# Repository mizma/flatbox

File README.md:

# Flatbox-ACR

_**No longer maintained.**_

**New Design is available [Here](https://github.com/mizma/ergoSHIFT/) with 11 button support and GP2040-CE firmware support planned**

_**Low profile hitbox-layout fightstick with Acrylic shell**_

This flatbox-acr design is based on [jfedor2/flatbox](https://github.com/jfedor2/flatbox) but with a few tweaks
(rev1.1 pcb has been redone from ground up):

[日本語はこちら](README_ja.md)

* Replaced the 3D printed case with Acrylic shell, allowing to insert printed artwork.
    * or marvel at the simplistic PCB...
    * Heavily inspired by y [Mille-Feuille](https://pomegd.booth.pm/items/2685530) by [@pomegd](https://twitter.com/pomegd)
* modified button layout to:
    * Accomodate for the clearance needed for acrylic cutting
    * To mimic the layout of the original Hitbox button layout(based off of official stencil)
* Silk screen update
    * Added small logo instead of text (flatbox acr)
    * added legends for each buttons (SQUARE, CIRCLE etc.)
    * moved logo to the bottom edge to minimize see-through when adding artwork on top
* Pattern changes
    * GND Fill
    * add vias to join gnd fill
    * moved traces slightly to avoid GND islands and thin GND fills
    * added reset button for Pro Micro board
* Remodeled Button Caps to accomodate for the increased case-height

Final product when assembled will look something like the following:

You can print any fan art using the [Stencil](hardware-rev1.1/images/Flatbox-ACR-Stencil_300dpi.png) 
to customize the looks as well.

(*) Artwork based on a trace of In-Game Screenshot + Official Fan-kit (©ARK SYSTEM WORKS)

There is currently one revision of the Flatbox-ACR.  They all use Kailh low profile (choc v1) mechanical keyboard switches.
The table below lists their main features.  See the README for each version for details on how to make them.

version | [rev1.1](hardware-rev1.1) |
------- | ------------------------- |
case dimensions | 210x125x13.6mm |
compatibility (using provided firmware) | PC, PS3, Xinput, Switch |
add-on board | Sparkfun Qwiic Pro Micro |
onboard chip | - |
port | USB-C |
SMT assembly required | no |
firmware | [ATmega32U4](firmwares_atmega32u4) |

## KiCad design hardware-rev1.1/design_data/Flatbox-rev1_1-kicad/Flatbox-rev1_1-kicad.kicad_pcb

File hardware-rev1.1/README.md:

# Flatbox-ACR rev1.1

[日本語はこちら](README_ja.md)

This is rev1.1 of the Flatbox-ACR. In this version an Arduino Pro Micro is soldered onto the main PCB.

To make one you will need:

* [acrylic shell](acrylic-shell)
    * Top layers in 2mm,3mm,2mm thickness
    * Bottom layers in 3mm thickness x 2
* [the Flatbox-ACR PCB](pcb)
* Arduino Pro Micro [SparkFun Qwiic Pro Micro - USB-C (ATmega32U4)](https://www.sparkfun.com/products/15795)
* 12x Kailh low profile (choc v1) switches of your choice
    * I use Kailh Choc v1 Red Pro (Linear and low activation force: 35±10gf with actuation travel: 1.5±0.5mm)
    * Light Blue (gChoc) can be used for even lower actuation force.
* (optionally) 12x Kailh low profile hotswap sockets
* [3D printed buttoncaps](../3d-printed-buttoncaps)
* 6x 6x6x5mm tact switches
    * I Used OMRON B3F-1000 but other similar products with same footprint should work
    * Selecting switches with height higher than 7mm will result in the switch extruding from the case
* 1x 3x6x4.3 horizontal tact switch
    * https://www.newegg.com/p/2S7-01KR-035X0
    * https://shop.yushakobo.jp/collections/all-keyboard-parts/products/a1600ed-01-1
    * [schematics](images/tactile-switch_3x6x4.3.jpg)
* 7x M3 screws (length 20mm)
    * Acryl top 2mm * 2 + 3mm = 7mm
    * PCB 1.6mm
    * Acryl bottom 3mm * 2 = 6mm
    * Rubber feet screw depth = 3mm (using rubber feet below.  adjust for your part)
    * Rubber feet total depth = 8mm (using rubber feet below.  adjust for your part)
    * M3 nut height = 2mm
    * min length = 19.6mm (using rubber feet below.  adjust for your part)
    * max length = 22.6mm (using rubber feet below.  adjust for your part)
* 7x M3 nut and acompanying rubber feet
    * Rubber feet Tochigiya [TM-TK-15](https://www.monotaro.com/p/0933/2486/?displayId=5)
    * The position of the holes are intended for feet radius of less than 8mm
* a soldering iron
    * something with enough power is better 
      (i.e. [Hakko FX 600](https://www.hakko.com/japan/products/hakko_fx600_set.html))
    * I recommend changin tips to D type for most Through-hole soldering, or C type if you plan to
      solder SMT as well. (default B tips are the harder to use for most PCB soldering)
    * Use 230C ~ 250C temp recommended (can be changed if you know your way around)

## Assembly Instructions

### Ordering PCB

I used [JLCPCB](https://jlcpcb.com/).  Just upload the gerber files in [pcb](pcb) and keep most parameters default.
You may change PCB Qty and PCB Color if you like.  All other parameters should be kept the same.

### Ordering 3D Printed Buttons

If you have a 3D printer, print at your own will.  Files are found [here](../3d-printed-buttoncaps/).

* [Flatbox-ACR-ButtonCapBig.stl](../3d-printed-buttoncaps/Flatbox-ACR-ButtonCapBig.stl) 
  is used for the thumb button. 1 board needs 1 of this button.
* [Flatbox-ACR-Buttoncap.stl](../3d-printed-buttoncaps/Flatbox-ACR-ButtonCapBig.stl) is used for all ther buttons.
  1 board needs 11 of this button.
* [Flatbox-ACR-FullSetButtonCaps.stl](../3d-printed-buttoncaps/Flatbox-ACR-FullSetButtonCaps.stl) is an STL file 
  containing 1 full set of buttons (11 small and 1 big.).  If your 3D printing service allows 12 or more shells,
  it may be cheaper to print in one batch using this STL file.
    * Print size needs to be bigger than X：99.0000mm x Y： 93.5000mm x Z： 6.0000mm

Insertion portion may need to be adjusted in size for your 3D Printer and settings to fit snugly to the switch.
You may use some of the printer features but if that doesn't work, you might want to edit the original model.
Model data are found in the same directory in a [FreeCAD](https://www.freecadweb.org/) file format.

Also, since the insertion portion requires a fairly tight tolerance which is not easily achieved by 3D printers.
To that extent, the models are modelled slightly on the larger side.  I have had fairly good results with 
this model using SLS Nylon print but sometimes it is too large.  Which can be filed down to fit.

#### Materials Consideration

* Nylon
    * May be a good place to start for tensile strength and good chemical stability.
    * can be pretty strong if printed using SLS process at some printing services
    * may be prone to warping.  not good for humid places.
* UV Resin
    * Also pretty strong as a material, and stronger to humidity.
    * Maybe slightly more brittle than Nylon

### Ordering Acrylic cuts

I use [Elecrow](https://www.elecrow.com/acrylic-cutting.html) to cut acrylic.

Upload the .zip file in [acrylic-shell](acrylic-shell/) to the Elecrow Acrylic cut service to order.
.Zip file includes the dxf file and the dimentions.txt file.  PDF is just for reference.

Layer 01 and 02 should be made of 3mm thickness.

For the top 3 layers, there are two options:

1. Print Layer 03 at 2mm, 04 at 2mm x 2.
    * This will produce the flatbox-acr at 13.6mm at the body (excl. rubber feet and buttons) at the cost of reset 
      switch not being covered.
2. Print Layer 03 at 2mm, 04 at 3mm and layer 05 at 2mm.
    * This will produce the flatbox-acr at 14.6mm at the body (excl. rubber feet and buttons).  Reset switch will 
      be covered at the cost of thickness and less button extrusion. (may want to tweak the button caps to have 
      more thickness)

The original design file (FreeCAD file) can be found [here](./design_data/acryl-design/).

The Acrylic should look like the following (with PCB stacked)

(*) Above image uses two Layer 4 at 2mm (exposed reset switch but 1mm thinner)

### Assembly

1. Solder all the Choc v1 switches and the tactile switches.  make sure you populate the side with the logo.
    * If you populate the side with the logo, the parts only goes in in the correct orientation.
    * If you use the hot-swap sockets, those will go on the back. (see silk screen on back side for orientation)
        * For hotswap sockets, pre-solder one side of the pad on PCB, place the socket, heat the pre-solder while
          pressing down on the socket to attach the socket.  After It is attached, solder the other side fully
          and then add more solder on the pre-soldered side.
2. Solder the Pro Micro Qwiic from the bottom side of the PCB up into the slit (USB socket should be between
   the cut-outs on the board, facing up) (Following instruction is how I did it.  There may be other ways)
    1.  First, mask the back side holes on the PCB with masking tape, and poke a small hole in each Through-hole
        with a needle. (This is to stop creating solder filets on the side the ProMicro will be soldered to.
        
    2. Insert a short (2~3cm) tin coated wire in the hole and solder onto the board.  Then cut the excess wire
       on the front side.

    3. Remove the masking tape.  The back side should have a flat solder filled hole with wires coming out 
       the middle.
       
    4. Place the Pro-Micro into the wires, tape it down to place.  Also tape the entire front side of 
       the soldered through-holes so the wires don't fall when solder melts.
       
    5. Solder the Pro-Micro to the tin-coated wire.
       
3. stack the Acryl and PCB in following order: Layer 01, Layer 02, PCB, Layer 03, Layer 04 and Layer 05.
    * If you use 2 Layer 4s, the order should be 01, 02, 03, 04, 04.
4. Screw on the M3 screws with the nut on all 7 locations.  Rubber feet should be inserted at least in the 4 
   corners between the nut and the acrylic.

It should look like the following when assembled.

### Pro-Tip 1. Filing the Acrylic Edges

Acrylic Edges after laser cutting can be quite sharp and do not feel good.
You may want to file the edges with sandpaper (#400 is a nice place to start) to remove the edges 
on the top acrylic layer so it does not feel bad.

### Pro-Tip 2. Customizing design

You can also insert some artwork below the top acrylic layer as below:

(*) Above sample Artwork based on a trace of In-Game Screenshot + Official Fan-kit (©ARK SYSTEM WORKS)

Stencil for the artwork can be found [HERE](images/Flatbox-ACR-Stencil_300dpi.png).  The stencil is in
300dpi so print the image at 300dpi to adjust size. [Stencil with key labels](images/Flatbox-ACR-Stencil_with_key_label_300dpi.png)
is also available.

To cut the stencil, use one of the top acrylic plates as cutting guides (don't trust the acuracy
of the printed stencil mark, they are good enough to use as design guide, but not acurate enough for 
final cutting guide).  It is easy to cut if you tape the plate on top of the print.

## License and Acknowlegements

PCB design licensed under [CC BY-SA 4.0](https://creativecommons.org/licenses/by-sa/4.0/) by mizma, derived from
[jfedor2/flatbox](https://github.com/jfedor2/flatbox) rev1.1 as of 2022/07/18

Acrylic sandwitching shell heavily inspired by [Mille-Feuille](https://pomegd.booth.pm/items/2685530) 
by [@pomegd](https://twitter.com/pomegd)

PCB design uses the following libraries or derivatives of the design:

* [jfedor2/flatbox](https://github.com/jfedor2/flatbox) by [jfedor2](https://github.com/jfedor2) ([CC BY-SA 4.0](https://creativecommons.org/licenses/by-sa/4.0/))
* [keyswitches.pretty](https://github.com/daprice/keyswitches.pretty) by [daprice](https://github.com/daprice) ([CC BY-SA 4.0](https://creativecommons.org/licenses/by-sa/4.0/))
* [ProMicroKiCad](https://github.com/Biacco42/ProMicroKiCad) by [Biacco42](https://github.com/Biacco42), derived from [teensy\_library](https://github.com/XenGi/teensy_library) by Ricardo Band ([MIT License](https://opensource.org/licenses/mit-license.php))

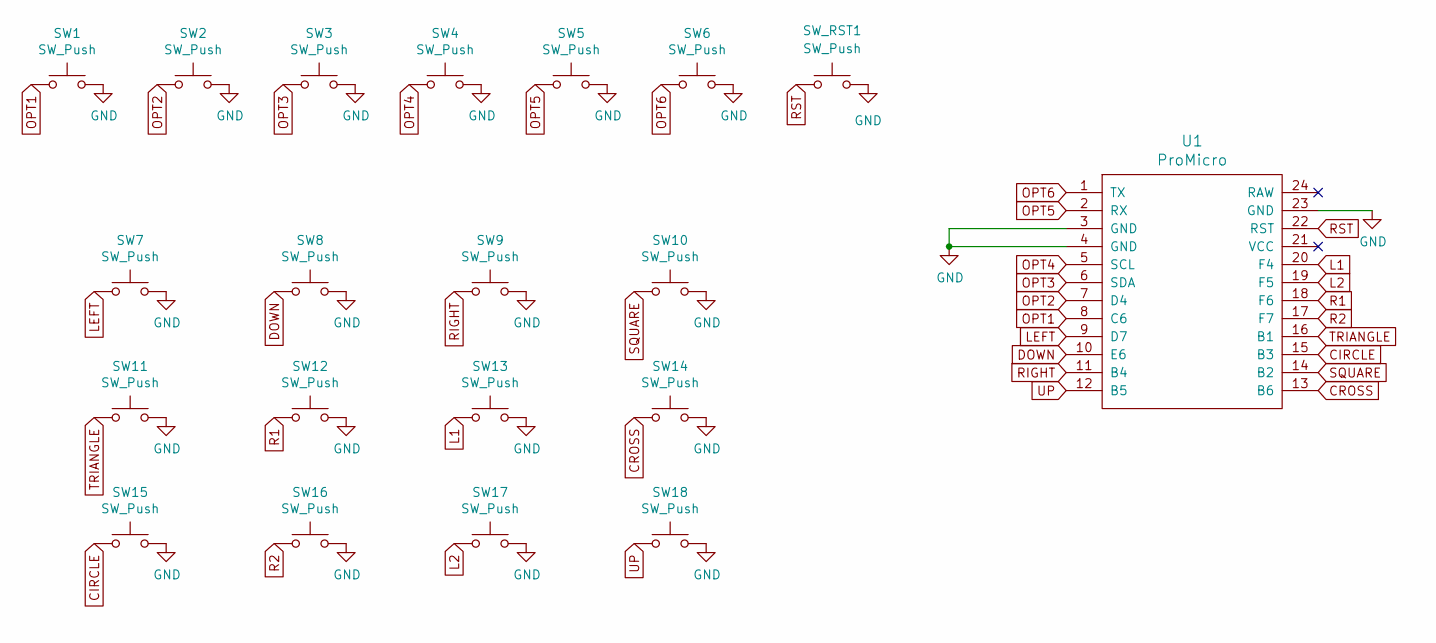
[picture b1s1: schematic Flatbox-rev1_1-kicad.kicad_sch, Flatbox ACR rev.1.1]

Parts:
SW1, SW2, SW3, SW4, SW5, SW6: SW_Push; SW_PUSH_6mm_H5mm
SW7, SW8, SW9, SW10, SW11, SW12, SW13, SW14, SW15, SW16, SW17, SW18: SW_Push; Kailh_socket_PG1350_optional
SW_RST1: SW_Push; SW_Tactile_Yushakobo 3x6x4.3mm
U1: ProMicro

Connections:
CIRCLE: SW15.1, U1.15 (B3)
CROSS: SW14.1, U1.13 (B6)
DOWN: SW8.1, U1.10 (E6)
GND: SW1.2, SW2.2, SW3.2, SW4.2, SW5.2, SW6.2, SW7.2, SW8.2, SW9.2, SW10.2, SW11.2, SW12.2, SW13.2, SW14.2, SW15.2, SW16.2, SW17.2, SW18.2, SW_RST1.2, U1.3 (GND), U1.4 (GND), U1.23 (GND)
L1: SW13.1, U1.20 (F4)
L2: SW17.1, U1.19 (F5)
LEFT: SW7.1, U1.9 (D7)
OPT1: SW1.1, U1.8 (C6)
OPT2: SW2.1, U1.7 (D4)
OPT3: SW3.1, U1.6 (SDA)
OPT4: SW4.1, U1.5 (SCL)
OPT5: SW5.1, U1.2 (RX)
OPT6: SW6.1, U1.1 (TX)
R1: SW12.1, U1.18 (F6)
R2: SW16.1, U1.17 (F7)
RIGHT: SW9.1, U1.11 (B4)
RST: SW_RST1.1, U1.22 (RST)
SQUARE: SW10.1, U1.14 (B2)
TRIANGLE: SW11.1, U1.16 (B1)
UP: SW18.1, U1.12 (B5)

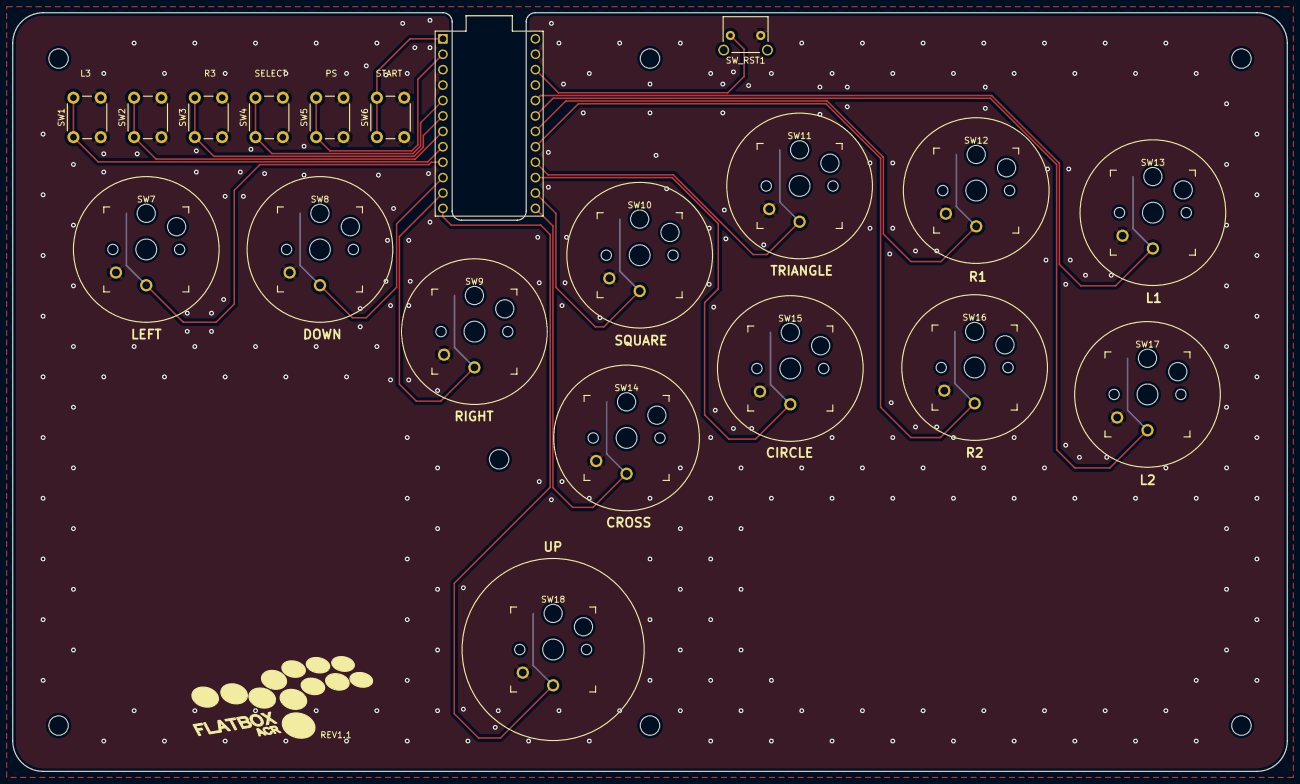
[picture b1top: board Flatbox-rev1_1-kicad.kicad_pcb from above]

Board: 2 copper layers, 210.0 x 125.0 mm, 20 parts (0 on the bottom side), 20 nets.

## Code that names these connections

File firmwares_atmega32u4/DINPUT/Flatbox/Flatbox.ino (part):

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#define PIN_DOWN      7
#define PIN_LEFT      6
#define PIN_RIGHT     8
#define PIN_CROSS     10
#define PIN_CIRCLE    14
#define PIN_TRIANGLE  15
#define PIN_SQUARE    16
#define PIN_L1        21
#define PIN_L2        20
#define PIN_R1        19
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#define PIN_DOWN      9
#define PIN_LEFT      8
#define PIN_RIGHT     10
#define PIN_CROSS     18
#define PIN_CIRCLE    21
#define PIN_TRIANGLE  14
#define PIN_SQUARE    7
#define PIN_L1        15
#define PIN_L2        19
#define PIN_R1        16
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  pinMode(PIN_DOWN, INPUT_PULLUP);
  pinMode(PIN_LEFT, INPUT_PULLUP);
  pinMode(PIN_RIGHT, INPUT_PULLUP);
  pinMode(PIN_CROSS, INPUT_PULLUP);
  pinMode(PIN_CIRCLE, INPUT_PULLUP);
  pinMode(PIN_TRIANGLE, INPUT_PULLUP);
  pinMode(PIN_SQUARE, INPUT_PULLUP);
  pinMode(PIN_L1, INPUT_PULLUP);
  pinMode(PIN_L2, INPUT_PULLUP);
  pinMode(PIN_R1, INPUT_PULLUP);
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       digitalRead(PIN_LEFT) == LOW,
       digitalRead(PIN_RIGHT) == LOW);

  if (digitalRead(PIN_SQUARE) == LOW) {
    report.buttons |= 1 << 0;
    report.squareAxis = 0xff;
  }
  if (digitalRead(PIN_CROSS) == LOW) {
    report.buttons |= 1 << 1;
    report.crossAxis = 0xff;
  }
  if (digitalRead(PIN_CIRCLE) == LOW) {
    report.buttons |= 1 << 2;
    report.circleAxis = 0xff;
  }
  if (digitalRead(PIN_TRIANGLE) == LOW) {
    report.buttons |= 1 << 3;
    report.triangleAxis = 0xff;
  }
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
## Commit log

2022-07-19 added STL for full set print orders. added logo for front silk
2022-07-19 removed unused logo art data
2022-07-19 moved original design files to original-hardware directory
2022-07-19 moved supporting files to original-hardware directory
2022-07-19 added note about fork date and link to original design
2022-07-19 initial modify for Flatbox-ACR
2022-07-19 fixed README for nuances. added PCB image
2022-07-19 added acrylic cut data and gerber files for PCB. update Readme.
2022-07-19 fix layout issues in dxf
2022-07-19 added warning
2022-07-19 fixed some issues with acrylic cut and edge cut on PCB
2022-07-19 add design data
2022-07-19 add logo
2022-07-19 update logo
2022-07-22 remove rev1 data. abandoned
2022-07-22 add hardware rev1.1 design
2022-07-22 rename to appropriate height
2022-07-22 fix acryl layer naming. added missing measurements in button layout file.
2022-07-22 fixed rev designation
2022-07-22 added buttoncap drawing
2022-07-23 first draft of Flatbox ACR ButtonCap
2022-07-23 fixed stl mesh. added fullset stl file
2022-07-23 remove original Flatbox buttoncaps (not applicable to ACR version)
2022-07-24 fixed README
2022-07-24 added TODO in firmware README. added stencil for illustrations
2022-07-31 fix SOCD and add GAFRO as well as reverse Up/Down feature
2022-07-31 fix typo
2022-07-31 fix ignore
2022-07-31 remove backup data
2022-08-02 reorganize firmware directory and added fork of LUFAHybridFightstick from CrazyRedMachine
2022-08-02 remove analog code, fix SOCD Config.
2022-08-02 modified configuration features. added .hex file
2022-08-02 fix README to match updated firmware
2022-08-02 revised Readme for firmware and added AllNeutral SOCD to DINPUT firmware
2022-08-02 fix some old README text to match current implementation
2022-08-02 added building instructions
2022-08-02 fixed typo
2022-08-02 fix some obsolete descriptions
2022-08-02 make table more legible
2022-08-02 add LICENSE
2022-08-02 fix license
2022-08-02 fix LICENSE file
2022-08-03 clarify README
2022-08-03 Clarifications in README
2022-08-03 add ASSY image
2022-08-03 added building instructions with photos
2022-08-03 Fix wrong instruction.
2022-08-03 remove old image
2022-08-03 add stencil with labels
2022-08-04 add hotkey cheat-sheet
2022-08-04 add image for cutting stencil
2022-08-05 added Japanese README
2022-08-09 added image with button caps. tweak button height.
2022-08-09 update on button caps.
2022-08-09 added DMM.Make creators market link in Readme
2022-08-09 removed WIP notice
2022-09-01 revised rev1.1 to remove unnecessary extrusion
2023-12-25 Update README.md
    Link to New project

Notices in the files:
hardware-rev1.1/README.md:
License and Acknowlegements:
PCB design licensed under [CC BY-SA 4.0](https://creativecommons.org/licenses/by-sa/4.0/) by mizma, derived from
[jfedor2/flatbox](https://github.com/jfedor2/flatbox) rev1.1 as of 2022/07/18
Acrylic sandwitching shell heavily inspired by [Mille-Feuille](https://pomegd.booth.pm/items/2685530)
PCB design uses the following libraries or derivatives of the design:
[jfedor2/flatbox](https://github.com/jfedor2/flatbox) by [jfedor2](https://github.com/jfedor2) ([CC BY-SA 4.0](https://creativecommons.org/licenses/by-sa/4.0/))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
